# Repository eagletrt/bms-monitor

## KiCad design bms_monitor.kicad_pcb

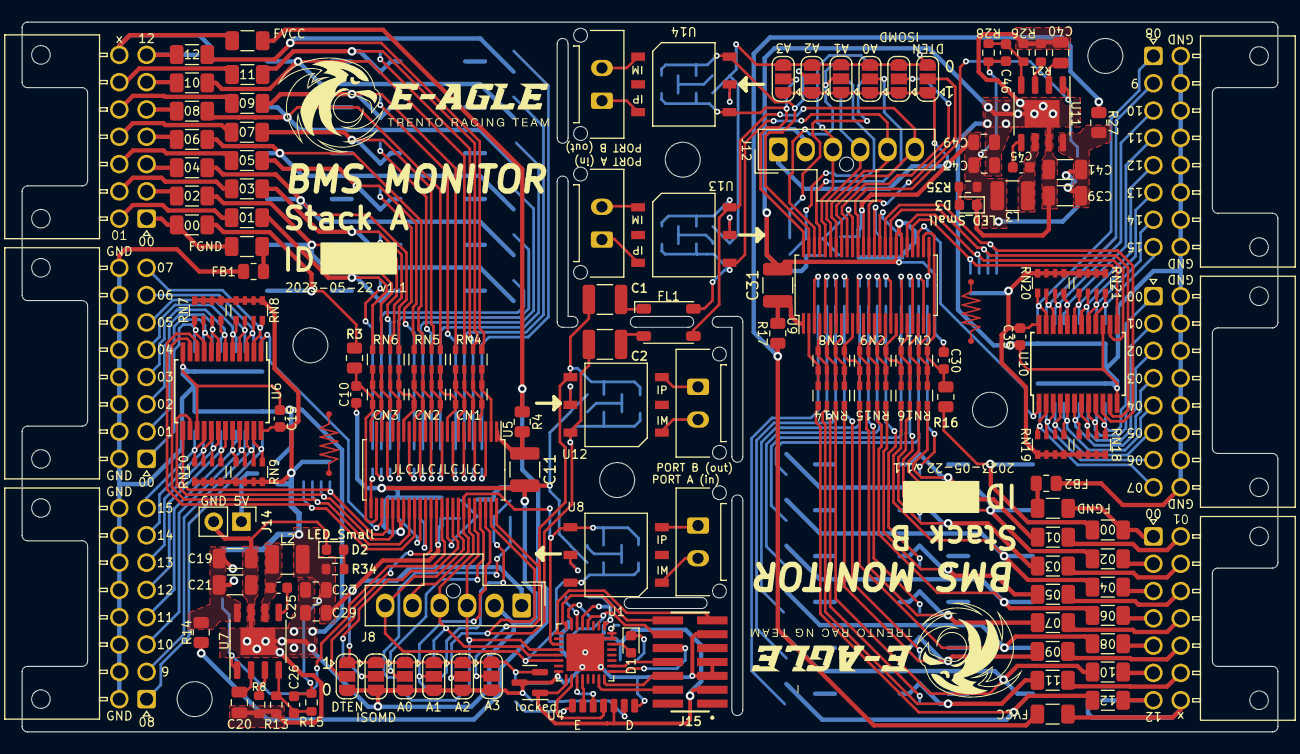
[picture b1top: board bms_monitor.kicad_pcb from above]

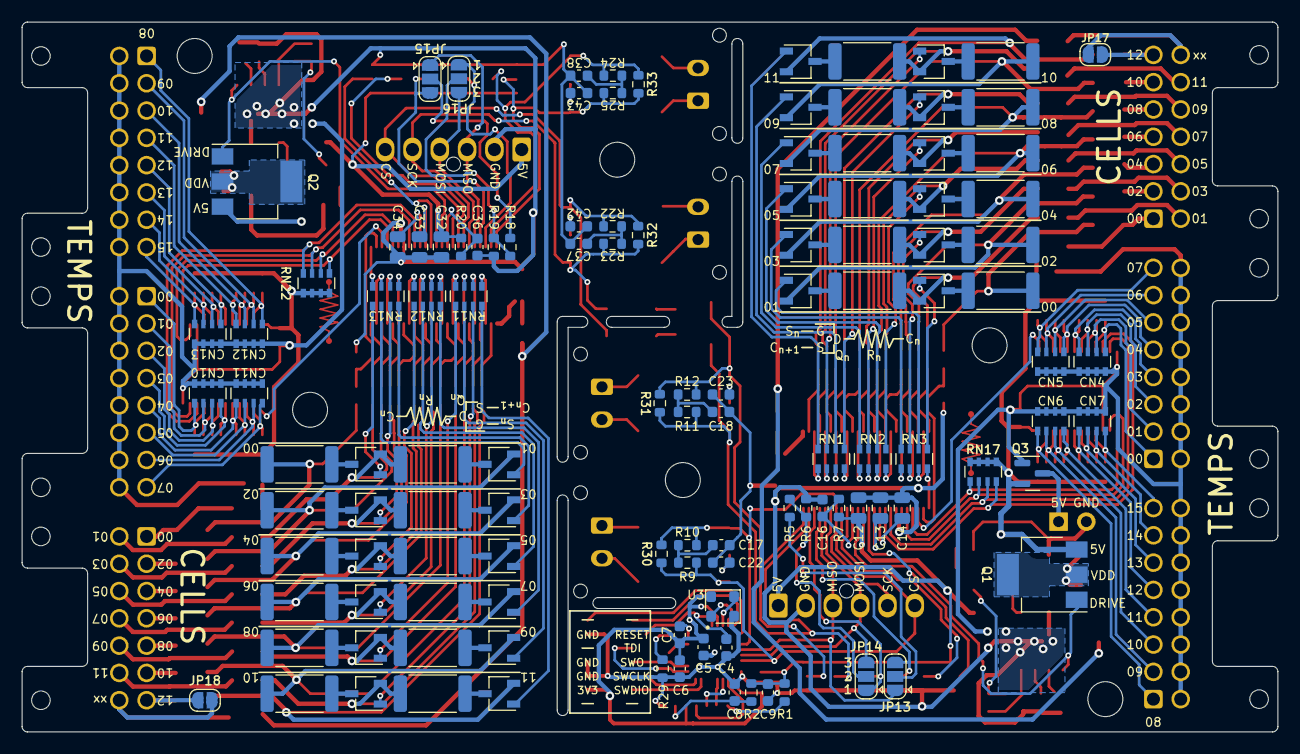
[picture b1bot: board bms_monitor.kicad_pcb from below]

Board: 2 copper layers, 115.0 x 65.0 mm, 256 parts (117 on the bottom side), 286 nets.

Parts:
C1, C2: 10nF 100V; C_1210_3225Metric
C4, C5, C6, C7, C8, C9, C15, C25, C35, C45: 100nF; C_0603_1608Metric
C10, C17, C18, C22, C23, C30, C37, C38, C42, C43: 10nF; C_0603_1608Metric
C11, C31: 100nF 100V; C_1210_3225Metric
C12, C13, C14, C20, C32, C33, C34, C40: 1uF; C_0805_2012Metric
C16, C36: F; C_0603_1608Metric
C19, C21, C39, C41: 1uF 100V; C_1206_3216Metric
C26, C46: 680pF; C_0603_1608Metric
C27, C29, C47, C49: 10uF; C_0805_2012Metric
CN1, CN2, CN3, CN8, CN9, CN14: 10nF; R_Array_Convex_4x0603
CN4, CN5, CN6, CN7, CN10, CN11, CN12, CN13: 100nF; R_Array_Convex_4x0603
D1: LED; LED_0603_1608Metric
D2, D3: LED_Small; LED_0603_1608Metric
F13, F14, F15, F16, F17, F18, F19, F20, F21, F22, F23, F24, F25: 2A; Fuse_1206_3216Metric
FB1, FB2: 600R; R_0805_2012Metric
FL1: ACT45B-101-2P-TL003; ACT45B-xxx-2P-TL003
Fa0, Fa1, Fa2, Fa3, Fa4, Fa5, Fa6, Fa7, Fa8, Fa9, Fa10, Fa11, Fa12, Fa13, Fa14: 2A; Fuse_1206_3216Metric
Fb3, Fb14: 2A; Fuse_1206_3216Metric
H1, H2, H3, H4, H5, H6: MountingHole; MountingHole_3.2mm_M3_ISO14580
J1, J2, J3, J4: Conn_01x02; Molex_Micro-Fit_3.0_43650-0215_1x02_P3.00mm_Vertical
J5, J9: CELLS; Molex_Nano-Fit_105314-xx14_2x07_P2.50mm_Horizontal
J6, J10: TEMP0; Molex_Nano-Fit_105314-xx16_2x08_P2.50mm_Horizontal
J7, J11: TEMP1; Molex_Nano-Fit_105314-xx16_2x08_P2.50mm_Horizontal
J8, J12: Conn_01x05; Molex_Nano-Fit_105309-xx06_1x06_P2.50mm_Vertical
J14: 5V; PinHeader_1x02_P2.54mm_Vertical
J15: Conn_ST_STDC14; SAMTEC_FTSH-107-01-L-DV-K-TR
JP1, JP7: A0; SolderJumper-3_P1.3mm_Open_RoundedPad1.0x1.5mm
JP2, JP8: A1; SolderJumper-3_P1.3mm_Open_RoundedPad1.0x1.5mm
JP3, JP9: A2; SolderJumper-3_P1.3mm_Open_RoundedPad1.0x1.5mm
JP4, JP10: A3; SolderJumper-3_P1.3mm_Open_RoundedPad1.0x1.5mm
JP5, JP11: DTEN; SolderJumper-3_P1.3mm_Open_RoundedPad1.0x1.5mm
JP6, JP12: ISOMD; SolderJumper-3_P1.3mm_Open_RoundedPad1.0x1.5mm
JP13, JP15: IBIAS; SolderJumper-3_P1.3mm_Open_RoundedPad1.0x1.5mm
JP14, JP16: ICMP; SolderJumper-3_P1.3mm_Open_RoundedPad1.0x1.5mm
JP17, JP18: isoIP; SolderJumper-2_P1.3mm_Open_RoundedPad1.0x1.5mm
L2, L3: 33uH; L_1210_3225Metric
Q1, Q2: NSS1C201MZ4; SOT-223
Q3: PMV65XP; SOT-23
Qda0, Qda1, Qda2, Qda3, Qda4, Qda5, Qda6, Qda7, Qda8, Qda9, Qda10, Qda11: BSS308PE; TSOT-23
Qdb0, Qdb1, Qdb2, Qdb3, Qdb4, Qdb5, Qdb6, Qdb7, Qdb8, Qdb9, Qdb10, Qdb11: BSS308PE; TSOT-23
R1, R2: 47R; R_0603_1608Metric
R3, R4, R14, R16, R17, R27: 100R; R_0805_2012Metric
R5, R6, R7, R18, R19, R20, R29: R; R_0603_1608Metric
R8, R21: 82k; R_0603_1608Metric
R9, R10, R11, R12, R22, R23, R24, R25: 51R; R_0603_1608Metric
R13, R26: 10k; R_0603_1608Metric
R15, R28: 39k; R_0603_1608Metric
R30, R31, R32, R33: 100; R_0603_1608Metric
R34, R35: 1K; R_0603_1608Metric
RN1, RN2, RN3, RN11, RN12, RN13: 3.3K; R_Array_Convex_4x0603
RN4, RN5, RN6, RN14, RN15, RN16: 100R; R_Array_Convex_4x0603
RN7, RN8, RN9, RN10, RN18, RN19, RN20, RN21: 27K; R_Array_Convex_4x0603
RN17, RN22: 10K; R_Array_Convex_4x0603
Rda0, Rda1, Rda2, Rda3, Rda4, Rda5, Rda6, Rda7, Rda8, Rda9, Rda10, Rda11: 10R; R_2512_6332Metric
Rdb0, Rdb1, Rdb2, Rdb3, Rdb4, Rdb5, Rdb6, Rdb7, Rdb8, Rdb9, Rdb10, Rdb11: 10R; R_2512_6332Metric
U1: STM32L432KBUx; QFN-32-1EP_5x5mm_P0.5mm_EP3.45x3.45mm
U3: DSC61XX; VLGA-4_2x2.5mm_P1.65mm
U4: TFBS4652
U5, U9: LTC6811-1; SSOP-48_5.3x12.8mm_P0.5mm
U6, U10: 74HC4067PW,118; SSOP-24_5.3x8.2mm_P0.65mm
U7, U11: MP4541; SOIC-8-1EP_3.9x4.9mm_P1.27mm_EP2.514x3.2mm
U8, U12, U13, U14: SM91502ALA
locked: MCP1812AT-033-TT; SOT-23

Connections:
+3.3V: C5.1, C6.1, C7.1, J15.3 (VCC), U1.1 (VDD), U1.5 (VDDA), U1.17 (VDD), U3.4 (VDD), U4.5 (VCCIO), locked.1 (Vout)
+5V: C9.1, C12.2, C15.2, C26.1, C27.1, C29.1, J8.1, JP1.1 (A), JP2.1 (A), JP3.1 (A), JP4.1 (A), JP5.1 (A), JP6.1 (A), L2.2, Q1.3 (E), Q3.2 (S), R1.2, R2.2, R7.1, R15.1, R34.1, RN7.1 (R1.1), RN7.2 (R2.1), RN7.3 (R3.1), RN7.4 (R4.1), RN8.1 (R1.1), RN8.2 (R2.1), RN8.3 (R3.1), RN8.4 (R4.1), RN9.1 (R1.1), RN9.2 (R2.1), RN9.3 (R3.1), RN9.4 (R4.1), RN10.1 (R1.1), RN10.2 (R2.1), RN10.3 (R3.1), RN10.4 (R4.1), RN17.1 (R1.1), RN17.2 (R2.1), RN17.3 (R3.1), RN17.4 (R4.1), U5.37 (VREG), U6.24 (VCC), locked.2 (Vin)
/CLK: U1.6 (PA0), U3.3 (OUT)
/CS: J8.6, R9.1, R30.1, U1.14 (PB0), U5.41 (CSB(IMA)), U8.6
/IA+_A: J8.5, R10.2, R30.2, U1.11 (PA5), U5.42 (SCK(IPA)), U8.4
/IAC_A: C22.2, U8.5
/IB+_B: JP10.2 (C), R25.2, R33.2, U9.48 (IPB), U14.4
/IB-_B: JP9.2 (C), R24.1, R33.1, U9.47 (IMB), U14.6
/IBC_B: C43.2, U14.5
/MISO: J8.3, JP13.1 (A), U1.12 (PA6), U5.44 (SDO(NC))
/MOSI: J8.4, JP14.3 (B), U1.13 (PA7), U5.43 (SDI(NC))
/STACK_A_IA+: J3.1, U8.3
/STACK_A_IA-: J3.2, U8.1
/STACK_A_IB+: J4.1, U12.3
/STACK_A_IB-: J4.2, U12.1
/STACK_B_IA+: J1.1, U13.3
/STACK_B_IA-: J1.2, U13.1
/STACK_B_IB+: J2.1, U14.3
/STACK_B_IB-: J2.2, U14.1
/SWCLK: J15.6 (JCLK/SWCLK), U1.24 (PA14)
/SWDIO: J15.4 (JTMS/SWDIO), U1.23 (PA13)
/SWO: J15.8 (JTDO/SWO), U1.26 (PB3)
/StackA/A0: JP1.2 (C), JP13.3 (B), U5.45 (IBIAS)
/StackA/A1: JP2.2 (C), JP14.1 (A), U5.46 (ICMP)
/StackA/A2: C2.1, JP3.2 (C), R11.1, R31.1, U5.47 (IMB), U12.6
/StackA/A3: C1.1, JP4.2 (C), R12.2, R31.2, U5.48 (IPB), U12.4
/StackA/C00: C10.2, CN3.1 (R1.1), R3.2, U5.26 (C0)
/StackA/C01: CN3.2 (R2.1), CN3.8 (R1.2), RN6.1 (R1.1), U5.24 (C1)
/StackA/C02: CN3.3 (R3.1), CN3.7 (R2.2), RN6.2 (R2.1), U5.22 (C2)
/StackA/C03: CN3.4 (R4.1), CN3.6 (R3.2), RN6.3 (R3.1), U5.20 (C3)
/StackA/C04: CN2.1 (R1.1), CN3.5 (R4.2), RN6.4 (R4.1), U5.18 (C4)
/StackA/C05: CN2.2 (R2.1), CN2.8 (R1.2), RN5.1 (R1.1), U5.16 (C5)
/StackA/C06: CN2.3 (R3.1), CN2.7 (R2.2), RN5.2 (R2.1), U5.14 (C6)
/StackA/C07: CN2.4 (R4.1), CN2.6 (R3.2), RN5.3 (R3.1), U5.12 (C7)
/StackA/C08: CN1.1 (R1.1), CN2.5 (R4.2), RN5.4 (R4.1), U5.10 (C8)
/StackA/C09: CN1.2 (R2.1), CN1.8 (R1.2), RN4.1 (R1.1), U5.8 (C9)
/StackA/C10: CN1.3 (R3.1), CN1.7 (R2.2), RN4.2 (R2.1), U5.6 (C10)
/StackA/C11: CN1.4 (R4.1), CN1.6 (R3.2), RN4.3 (R3.1), U5.4 (C11)
/StackA/C12: CN1.5 (R4.2), RN4.4 (R4.1), U5.2 (C12)
/StackA/CC00: Fa0.1, R3.1, Rda0.2
/StackA/CC01: Fa1.1, Qda0.2 (S), RN6.8 (R1.2), Rda1.2
/StackA/CC02: Fa2.1, Qda1.2 (S), RN6.7 (R2.2), Rda2.2
/StackA/CC03: Fa3.1, Qda2.2 (S), RN6.6 (R3.2), Rda3.2
/StackA/CC04: Fa4.1, Qda3.2 (S), RN6.5 (R4.2), Rda4.2
/StackA/CC05: Fa5.1, Qda4.2 (S), RN5.8 (R1.2), Rda5.2
/StackA/CC06: Fa6.1, Qda5.2 (S), RN5.7 (R2.2), Rda6.2
/StackA/CC07: Fa7.1, Qda6.2 (S), RN5.6 (R3.2), Rda7.2
/StackA/CC08: Fa8.1, Qda7.2 (S), RN5.5 (R4.2), Rda8.2
/StackA/CC09: Fa9.1, Qda8.2 (S), RN4.8 (R1.2), Rda9.2
/StackA/CC10: Fa10.1, Qda9.2 (S), RN4.7 (R2.2), Rda10.2
/StackA/CC11: Fa11.1, Qda10.2 (S), RN4.6 (R3.2), Rda11.2
/StackA/CC12: Fa12.1, Qda11.2 (S), RN4.5 (R4.2)
/StackA/DRIVE: Q1.1 (B), U5.38 (DRIVE), U7.1 (EN)
/StackA/DTEN: JP5.2 (C), U5.36 (SWTEN)
/StackA/IBC: C23.2, U12.5
/StackA/ISOMD: JP6.2 (C), U5.40 (ISOMD)
/StackA/MUX_A0: RN17.8 (R1.2), U5.33 (GPIO5), U6.10 (S0)
/StackA/MUX_A1: RN17.7 (R2.2), U5.32 (GPIO4), U6.11 (S1)
/StackA/MUX_A2: RN17.6 (R3.2), U5.29 (GPIO3), U6.14 (S2)
/StackA/MUX_A3: RN17.5 (R4.2), U5.28 (GPIO2), U6.13 (S3)
/StackA/MUX_OUT: U5.27 (GPIO1), U6.1 (COM)
/StackA/PSU_INPUT: C19.1, C21.1, Q1.2 (C), Q1.4 (C), R14.2, U7.8 (VIN)
/StackA/S00: RN3.8 (R1.2), U5.25 (S1)
/StackA/S01: RN3.7 (R2.2), U5.23 (S2)
/StackA/S02: RN3.6 (R3.2), U5.21 (S3)
/StackA/S03: RN3.5 (R4.2), U5.19 (S4)
/StackA/S04: RN2.8 (R1.2), U5.17 (S5)
/StackA/S05: RN2.7 (R2.2), U5.15 (S6)
/StackA/S06: RN2.6 (R3.2), U5.13 (S7)
/StackA/S07: RN2.5 (R4.2), U5.11 (S8)
/StackA/S08: RN1.8 (R1.2), U5.9 (S9)
/StackA/S09: RN1.7 (R2.2), U5.7 (S10)
/StackA/S10: RN1.6 (R3.2), U5.5 (S11)
/StackA/S11: RN1.5 (R4.2), U5.3 (S12)
/StackA/VDD: Fa13.1, R4.1, R14.1
/StackA/WDT: C16.1, R7.2, U5.39 (WDT)
/StackB/A0: JP7.2 (C), JP15.3 (B), U9.45 (IBIAS)
/StackB/A1: JP8.2 (C), JP16.1 (A), U9.46 (ICMP)
/StackB/C00: C30.2, CN14.1 (R1.1), R16.2, U9.26 (C0)
/StackB/C01: CN14.2 (R2.1), CN14.8 (R1.2), RN16.1 (R1.1), U9.24 (C1)
/StackB/C02: CN14.3 (R3.1), CN14.7 (R2.2), RN16.2 (R2.1), U9.22 (C2)
/StackB/C03: CN14.4 (R4.1), CN14.6 (R3.2), RN16.3 (R3.1), U9.20 (C3)
/StackB/C04: CN9.1 (R1.1), CN14.5 (R4.2), RN16.4 (R4.1), U9.18 (C4)
/StackB/C05: CN9.2 (R2.1), CN9.8 (R1.2), RN15.1 (R1.1), U9.16 (C5)
/StackB/C06: CN9.3 (R3.1), CN9.7 (R2.2), RN15.2 (R2.1), U9.14 (C6)
/StackB/C07: CN9.4 (R4.1), CN9.6 (R3.2), RN15.3 (R3.1), U9.12 (C7)
/StackB/C08: CN8.1 (R1.1), CN9.5 (R4.2), RN15.4 (R4.1), U9.10 (C8)
/StackB/C09: CN8.2 (R2.1), CN8.8 (R1.2), RN14.1 (R1.1), U9.8 (C9)
/StackB/C10: CN8.3 (R3.1), CN8.7 (R2.2), RN14.2 (R2.1), U9.6 (C10)
/StackB/C11: CN8.4 (R4.1), CN8.6 (R3.2), RN14.3 (R3.1), U9.4 (C11)
/StackB/C12: CN8.5 (R4.2), RN14.4 (R4.1), U9.2 (C12)
/StackB/CC00: F19.1, R16.1, Rdb0.2
/StackB/CC01: F25.1, Qdb0.2 (S), RN16.8 (R1.2), Rdb1.2
/StackB/CC02: F18.1, Qdb1.2 (S), RN16.7 (R2.2), Rdb2.2
/StackB/CC03: F24.1, Qdb2.2 (S), RN16.6 (R3.2), Rdb3.2
/StackB/CC04: F17.1, Qdb3.2 (S), RN16.5 (R4.2), Rdb4.2
/StackB/CC05: F23.1, Qdb4.2 (S), RN15.8 (R1.2), Rdb5.2
/StackB/CC06: F16.1, Qdb5.2 (S), RN15.7 (R2.2), Rdb6.2
/StackB/CC07: F22.1, Qdb6.2 (S), RN15.6 (R3.2), Rdb7.2
/StackB/CC08: F15.1, Qdb7.2 (S), RN15.5 (R4.2), Rdb8.2
/StackB/CC09: F21.1, Qdb8.2 (S), RN14.8 (R1.2), Rdb9.2
/StackB/CC10: F14.1, Qdb9.2 (S), RN14.7 (R2.2), Rdb10.2
/StackB/CC11: F20.1, Qdb10.2 (S), RN14.6 (R3.2), Rdb11.2
/StackB/CC12: F13.1, Qdb11.2 (S), RN14.5 (R4.2)
/StackB/CSB: FL1.3, J12.6, R22.1, R32.1, U9.41 (CSB(IMA)), U13.6
/StackB/DRIVE: Q2.1 (B), U9.38 (DRIVE), U11.1 (EN)
/StackB/DTEN: JP11.2 (C), U9.36 (SWTEN)
/StackB/GND: C30.1, C31.2, C32.1, C33.1, C34.1, C35.1, C36.2, C37.2, C38.2, C39.2, C40.2, C41.2, C42.1, C43.1, C47.2, C49.2, CN10.1 (R1.1), CN10.2 (R2.1), CN10.3 (R3.1), CN10.4 (R4.1), CN11.1 (R1.1), CN11.2 (R2.1), CN11.3 (R3.1), CN11.4 (R4.1), CN12.1 (R1.1), CN12.2 (R2.1), CN12.3 (R3.1), CN12.4 (R4.1), CN13.1 (R1.1), CN13.2 (R2.1), CN13.3 (R3.1), CN13.4 (R4.1), D3.1 (K), FB2.2, J10.9, J10.10, J10.11, J10.12, J10.13, J10.14, J10.15, J10.16, J11.9, J11.10, J11.11, J11.12, J11.13, J11.14, J11.15, J11.16, J12.2, JP7.3 (B), JP8.3 (B), JP9.3 (B), JP10.3 (B), JP11.3 (B), JP12.3 (B), R19.1, R21.1, R26.1, U9.30 (V-), U9.31 (V-), U10.12 (GND), U10.15 (~E), U11.7 (GND), U11.9 (EP)
/StackB/IA+: FL1.4, J12.5, R23.2, R32.2, U9.42 (SCK(IPA)), U13.4
/StackB/IAC: C42.2, U13.5
/StackB/IBIAS_2: J12.3, JP15.1 (A), U9.44 (SDO(NC))
/StackB/ICMP_2: J12.4, JP16.3 (B), U9.43 (SDI(NC))
/StackB/ISOMD: JP12.2 (C), U9.40 (ISOMD)
/StackB/MUX_A0: RN22.8 (R1.2), U9.33 (GPIO5), U10.10 (S0)
/StackB/MUX_A1: RN22.7 (R2.2), U9.32 (GPIO4), U10.11 (S1)
/StackB/MUX_A2: RN22.6 (R3.2), U9.29 (GPIO3), U10.14 (S2)
/StackB/MUX_A3: RN22.5 (R4.2), U9.28 (GPIO2), U10.13 (S3)
/StackB/MUX_OUT: U9.27 (GPIO1), U10.1 (COM)
/StackB/PSU_INPUT: C39.1, C41.1, Q2.2 (C), Q2.4 (C), R27.2, U11.8 (VIN)
/StackB/S00: RN13.8 (R1.2), U9.25 (S1)
/StackB/S01: RN13.7 (R2.2), U9.23 (S2)
/StackB/S02: RN13.6 (R3.2), U9.21 (S3)
/StackB/S03: RN13.5 (R4.2), U9.19 (S4)
/StackB/S04: RN12.8 (R1.2), U9.17 (S5)
/StackB/S05: RN12.7 (R2.2), U9.15 (S6)
/StackB/S06: RN12.6 (R3.2), U9.13 (S7)
/StackB/S07: RN12.5 (R4.2), U9.11 (S8)
/StackB/S08: RN11.8 (R1.2), U9.9 (S9)
/StackB/S09: RN11.7 (R2.2), U9.7 (S10)
/StackB/S10: RN11.6 (R3.2), U9.5 (S11)
/StackB/S11: RN11.5 (R4.2), U9.3 (S12)
/StackB/VCC: C32.2, C35.2, C46.1, C47.1, C49.1, J12.1, JP7.1 (A), JP8.1 (A), JP9.1 (A), JP10.1 (A), JP11.1 (A), JP12.1 (A), L3.2, Q2.3 (E), R20.1, R28.1, R35.1, RN18.1 (R1.1), RN18.2 (R2.1), RN18.3 (R3.1), RN18.4 (R4.1), RN19.1 (R1.1), RN19.2 (R2.1), RN19.3 (R3.1), RN19.4 (R4.1), RN20.1 (R1.1), RN20.2 (R2.1), RN20.3 (R3.1), RN20.4 (R4.1), RN21.1 (R1.1), RN21.2 (R2.1), RN21.3 (R3.1), RN21.4 (R4.1), RN22.1 (R1.1), RN22.2 (R2.1), RN22.3 (R3.1), RN22.4 (R4.1), U9.37 (VREG), U10.24 (VCC)
/StackB/VDD: Fb3.1, R17.1, R27.1
/StackB/WDT: C36.1, R20.2, U9.39 (WDT)
/TDI: J15.10 (JTDI/NC), U1.25 (PA15)
/UART2_RX: J15.13 (VCP_RX), U1.9 (PA3)
/UART2_TX: J15.14 (VCP_TX), U1.8 (PA2)
/~RESET: C4.2, J15.12 (~RST), U1.4 (NRST)
GND: C4.1, C5.2, C6.2, C7.2, C8.2, C9.2, C10.1, C11.2, C12.1, C13.1, C14.1, C15.1, C16.2, C17.2, C18.2, C19.2, C20.2, C21.2, C22.1, C23.1, C27.2, C29.2, CN4.1 (R1.1), CN4.2 (R2.1), CN4.3 (R3.1), CN4.4 (R4.1), CN5.1 (R1.1), CN5.2 (R2.1), CN5.3 (R3.1), CN5.4 (R4.1), CN6.1 (R1.1), CN6.2 (R2.1), CN6.3 (R3.1), CN6.4 (R4.1), CN7.1 (R1.1), CN7.2 (R2.1), CN7.3 (R3.1), CN7.4 (R4.1), D2.1 (K), FB1.2, J6.9, J6.10, J6.11, J6.12, J6.13, J6.14, J6.15, J6.16, J7.9, J7.10, J7.11, J7.12, J7.13, J7.14, J7.15, J7.16, J8.2, J14.2, J15.5 (GND), J15.7 (GND), J15.11 (GNDDetect), JP1.3 (B), JP2.3 (B), JP3.3 (B), JP4.3 (B), JP5.3 (B), JP6.3 (B), Q3.1 (G), R6.1, R8.1, R13.1, R29.2, U1.16 (VSS), U1.31 (PH3), U1.32 (VSS), U1.33 (VSS), U3.2 (GND), U4.7 (GND), U5.30 (V-), U5.31 (V-), U6.12 (GND), U6.15 (~E), U7.7 (GND), U7.9 (EP), locked.3 (GND)
unnamed: C1.2, FL1.1
unnamed: C2.2, FL1.2
unnamed: C8.1, R2.1, U4.6 (VCC)
unnamed: C11.1, R4.2, U5.1 (V+)
unnamed: C13.2, U5.35 (VREF1)
unnamed: C14.2, U5.34 (VREF2)
unnamed: C17.1, R9.2, R10.1
unnamed: C18.1, R11.2, R12.1
unnamed: C20.1, U7.2 (VCC)
unnamed: C25.1, U7.5 (BST)
unnamed: C25.2, L2.1, U7.6 (SW)
unnamed: C26.2, R13.2, R15.2, U7.4 (FB)
unnamed: C31.1, R17.2, U9.1 (V+)
unnamed: C33.2, U9.35 (VREF1)
unnamed: C34.2, U9.34 (VREF2)
unnamed: C37.1, R22.2, R23.1
unnamed: C38.1, R24.2, R25.1
unnamed: C40.1, U11.2 (VCC)
unnamed: C45.1, U11.5 (BST)
unnamed: C45.2, L3.1, U11.6 (SW)
unnamed: C46.2, R26.2, R28.2, U11.4 (FB)
unnamed: CN4.5 (R4.2), J7.1, RN7.5 (R4.2), U6.9 (I0)
unnamed: CN4.6 (R3.2), J7.2, RN7.6 (R3.2), U6.8 (I1)
unnamed: CN4.7 (R2.2), J7.3, RN7.7 (R2.2), U6.7 (I2)
unnamed: CN4.8 (R1.2), J7.4, RN7.8 (R1.2), U6.6 (I3)
unnamed: CN5.5 (R4.2), J7.5, RN8.5 (R4.2), U6.5 (I4)
unnamed: CN5.6 (R3.2), J7.6, RN8.6 (R3.2), U6.4 (I5)
unnamed: CN5.7 (R2.2), J7.7, RN8.7 (R2.2), U6.3 (I6)
unnamed: CN5.8 (R1.2), J7.8, RN8.8 (R1.2), U6.2 (I7)
unnamed: CN6.5 (R4.2), J6.1, RN9.5 (R4.2), U6.23 (I8)
unnamed: CN6.6 (R3.2), J6.2, RN9.6 (R3.2), U6.22 (I9)
unnamed: CN6.7 (R2.2), J6.3, RN9.7 (R2.2), U6.21 (I10)
unnamed: CN6.8 (R1.2), J6.4, RN9.8 (R1.2), U6.20 (I11)
unnamed: CN7.5 (R4.2), J6.5, RN10.5 (R4.2), U6.19 (I12)
unnamed: CN7.6 (R3.2), J6.6, RN10.6 (R3.2), U6.18 (I13)
unnamed: CN7.7 (R2.2), J6.7, RN10.7 (R2.2), U6.17 (I14)
unnamed: CN7.8 (R1.2), J6.8, RN10.8 (R1.2), U6.16 (I15)
unnamed: CN10.5 (R4.2), J11.1, RN18.5 (R4.2), U10.9 (I0)
unnamed: CN10.6 (R3.2), J11.2, RN18.6 (R3.2), U10.8 (I1)
unnamed: CN10.7 (R2.2), J11.3, RN18.7 (R2.2), U10.7 (I2)
unnamed: CN10.8 (R1.2), J11.4, RN18.8 (R1.2), U10.6 (I3)
unnamed: CN11.5 (R4.2), J11.5, RN19.5 (R4.2), U10.5 (I4)
unnamed: CN11.6 (R3.2), J11.6, RN19.6 (R3.2), U10.4 (I5)
unnamed: CN11.7 (R2.2), J11.7, RN19.7 (R2.2), U10.3 (I6)
unnamed: CN11.8 (R1.2), J11.8, RN19.8 (R1.2), U10.2 (I7)
unnamed: CN12.5 (R4.2), J10.1, RN20.5 (R4.2), U10.23 (I8)
unnamed: CN12.6 (R3.2), J10.2, RN20.6 (R3.2), U10.22 (I9)
unnamed: CN12.7 (R2.2), J10.3, RN20.7 (R2.2), U10.21 (I10)
unnamed: CN12.8 (R1.2), J10.4, RN20.8 (R1.2), U10.20 (I11)
unnamed: CN13.5 (R4.2), J10.5, RN21.5 (R4.2), U10.19 (I12)
unnamed: CN13.6 (R3.2), J10.6, RN21.6 (R3.2), U10.18 (I13)
unnamed: CN13.7 (R2.2), J10.7, RN21.7 (R2.2), U10.17 (I14)
unnamed: CN13.8 (R1.2), J10.8, RN21.8 (R1.2), U10.16 (I15)
unnamed: D1.1 (K), R29.1
unnamed: D1.2 (A), U1.30 (PB7)
unnamed: D2.2 (A), R34.2
unnamed: D3.2 (A), R35.2
unnamed: F13.2, J9.7, JP18.1 (A)
unnamed: F14.2, J9.6
unnamed: F15.2, J9.5
unnamed: F16.2, J9.4
unnamed: F17.2, J9.3
unnamed: F18.2, J9.2
unnamed: F19.2, Fb14.2, J9.1
unnamed: F20.2, J9.13
unnamed: F21.2, J9.12
unnamed: F22.2, J9.11
unnamed: F23.2, J9.10
unnamed: F24.2, J9.9
unnamed: F25.2, J9.8
unnamed: FB1.1, Fa14.1
unnamed: FB2.1, Fb14.1
unnamed: Fa0.2, Fa14.2, J5.1
unnamed: Fa1.2, J5.8
unnamed: Fa2.2, J5.2
unnamed: Fa3.2, J5.9
unnamed: Fa4.2, J5.3
unnamed: Fa5.2, J5.10
unnamed: Fa6.2, J5.4
unnamed: Fa7.2, J5.11
unnamed: Fa8.2, J5.5
unnamed: Fa9.2, J5.12
unnamed: Fa10.2, J5.6
unnamed: Fa11.2, J5.13
unnamed: Fa12.2, J5.7, JP17.1 (A)
unnamed: Fa13.2, J5.14, JP17.2 (B)
unnamed: Fb3.2, J9.14, JP18.2 (B)
unnamed: J14.1, Q3.3 (D)
unnamed: JP13.2 (C), R5.2
unnamed: JP14.2 (C), R5.1, R6.2
unnamed: JP15.2 (C), R18.2
unnamed: JP16.2 (C), R18.1, R19.2
unnamed: Qda0.1 (G), RN3.1 (R1.1)
unnamed: Qda0.3 (D), Rda0.1
unnamed: Qda1.1 (G), RN3.2 (R2.1)
unnamed: Qda1.3 (D), Rda1.1
unnamed: Qda2.1 (G), RN3.3 (R3.1)
unnamed: Qda2.3 (D), Rda2.1
unnamed: Qda3.1 (G), RN3.4 (R4.1)
unnamed: Qda3.3 (D), Rda3.1
unnamed: Qda4.1 (G), RN2.1 (R1.1)
unnamed: Qda4.3 (D), Rda4.1
unnamed: Qda5.1 (G), RN2.2 (R2.1)
unnamed: Qda5.3 (D), Rda5.1
unnamed: Qda6.1 (G), RN2.3 (R3.1)
unnamed: Qda6.3 (D), Rda6.1
unnamed: Qda7.1 (G), RN2.4 (R4.1)
unnamed: Qda7.3 (D), Rda7.1
unnamed: Qda8.1 (G), RN1.1 (R1.1)
unnamed: Qda8.3 (D), Rda8.1
unnamed: Qda9.1 (G), RN1.2 (R2.1)
unnamed: Qda9.3 (D), Rda9.1
unnamed: Qda10.1 (G), RN1.3 (R3.1)
unnamed: Qda10.3 (D), Rda10.1
unnamed: Qda11.1 (G), RN1.4 (R4.1)
unnamed: Qda11.3 (D), Rda11.1
unnamed: Qdb0.1 (G), RN13.1 (R1.1)
unnamed: Qdb0.3 (D), Rdb0.1
unnamed: Qdb1.1 (G), RN13.2 (R2.1)
unnamed: Qdb1.3 (D), Rdb1.1
unnamed: Qdb2.1 (G), RN13.3 (R3.1)
unnamed: Qdb2.3 (D), Rdb2.1
unnamed: Qdb3.1 (G), RN13.4 (R4.1)
unnamed: Qdb3.3 (D), Rdb3.1
unnamed: Qdb4.1 (G), RN12.1 (R1.1)
unnamed: Qdb4.3 (D), Rdb4.1
unnamed: Qdb5.1 (G), RN12.2 (R2.1)
unnamed: Qdb5.3 (D), Rdb5.1
unnamed: Qdb6.1 (G), RN12.3 (R3.1)
unnamed: Qdb6.3 (D), Rdb6.1
unnamed: Qdb7.1 (G), RN12.4 (R4.1)
unnamed: Qdb7.3 (D), Rdb7.1
unnamed: Qdb8.1 (G), RN11.1 (R1.1)
unnamed: Qdb8.3 (D), Rdb8.1
unnamed: Qdb9.1 (G), RN11.2 (R2.1)
unnamed: Qdb9.3 (D), Rdb9.1
unnamed: Qdb10.1 (G), RN11.3 (R3.1)
unnamed: Qdb10.3 (D), Rdb10.1
unnamed: Qdb11.1 (G), RN11.4 (R4.1)
unnamed: Qdb11.3 (D), Rdb11.1
unnamed: R1.1, U4.1 (IREDA)
unnamed: R8.2, U7.3 (FREQ)
unnamed: R21.2, U11.3 (FREQ)
unnamed: U1.7 (PA1), U3.1 (OE)
unnamed: U1.18 (PA8), U4.4 (SD)
unnamed: U1.19 (PA9), U4.3 (TXD)
unnamed: U1.20 (PA10), U4.2 (RXD)

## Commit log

2023-03-16 pre production
    - footprints change
2023-03-16 pre production
    footprint change
2023-03-17 production candidate
    - footprint change
    - added ltc6811-2 full compatibility
2023-03-20 Addition
    -Added USART 2 to Programming connector
2023-03-23 fix
    added ltc gpio pull up resistor
2023-03-24 fabrication
    added fabrication files
2023-03-24 fix
    - added pmos for reverse polarity protection to prog pwr
    - fixed temp connectors numbering (silkscreen)
    - regenerated fabrication files
2023-04-14 doc: add datasheets
2023-04-14 fab: update pcb for fabrication
2023-05-22 fix
    - Changed oscillator footprint
    - tied mux enable to ground
    - Corrected power BJT's footprint
    - added 5V presence led
2023-05-23 upadate
    - updated fabrication output
    - added 3d models
    - updated bom
